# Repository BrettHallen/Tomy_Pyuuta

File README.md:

# Tomy Pyūta<br>トミーぴゅう太
Information about the Tomy Pyūta (TP1000), Pyūta Mk II (TP1007) and Pyūta Jr. (TP2001).  This computer was also seen in the West as the Tomy Tutor, but I don't have one of those and I'm sure there's plenty of English-language information already easily found.

Sorry about the mixed use of:
- ぴゅう太 (pyuuta)
- Pyuuta
- Pyuta
- Pyūta (pyuuta)
- Puuta (on motherboard)
- Mk II
- Mk 2
- mkII
- Mark 2
- Mark II
- etc.

### Pyūta TP1000

### Pyūta mkII TP1007
The motherboard names it as the TUTOR-MKII.

## YouTube Videos
### Pyūta (TP1000)
- [Part 1: Power On](https://youtu.be/n1GbW3sMFAQ)
- [Part 2: New Power Supply & Game Adaptor](https://youtu.be/_u84HEhmOtU)

### Pyūta mkII (TP1007)
- [Part 1: First Look](https://youtu.be/pd9VcPLzIxA)

## [Japanese G-BASIC Statements](/Japanese_G-BASIC)
My attempt at making sense of the unique Japanese version of BASIC (日本語G-BASIC) on the original ぴゅう太.

## [Universal Power Supply](/Tomy_Pyuuta_Power_Supply)
The Japanese ぴゅう太 is designed for a 100VAC input.<br>

The power supply outputs regulated +12VDC (via an LM7812), regulated -5VDC (via a TA78L005AP) and unregulated +5VDC (about +7.8V unloaded, 5.3V under load).  Yes, that is not a mistake ... the regulated -5V rail uses a 7805.<br>

The power LED is also connected to the -5V rail.<br>

I have designed a simple replacement as we use 240VAC here in Australia.<br>

It takes a regulated 12VDC input (3-4A) and generates the required ±5VDC via switching regulators, and passes the +12VDC straight through.<br>

## Pyūta mkII Video Mod
It seems that Tomy removed the baseband A/V output that was in the original TP1000 from the mkII, leaving it with just the RF modulated output.  I created a [quick schematic of the video output](/Schematics/Tomy_Pyuuta_mkII_AV) in the mkII to use as a basis, and found an [RC2014 expansion board that adds a TMS9918 video output](https://github.com/jblang/TMS9918A) which I could use as a reference.<br>

It seems to work okay!  I am planning to replace the TMS9918 with a [Pico9918](https://github.com/visrealm/pico9918) anyway.<br>

| Component | Original value | Modified value | Notes                                               |
|-----------|----------------|----------------|-----------------------------------------------------|
| R2        | 33Ω            | 75Ω            | Impedance matching                                  |
| R3        | 33Ω            | 0Ω link        |                                                     |
| R4        | 560Ω           | 470Ω           | Values are close, don't bother?                     |
| R5        | 8.2Ω           | Ferrite bead   |                                                     |
| C4        | 330pF          | 100nF to GND   | Connect from Q1 collector to GND                    |
| C49       | 47nF           | Remove         | 12V decoupling, not needed if RF modulator removed? |

## [Game Adaptor](/Pyuuta_Game_Adaptor)
My attempt at a homebrew version of the Pyūta Game Adaptor seeing as most of the information seems to have been lost.<br>

The Game Adaptor allows the original Pyūta (TP1000) to run 32KB cartridges designed for the Mk II (TP1007) and Jr. (TP2001).<br>

## Sources
- [yanataka60](https://github.com/yanataka60)

## Useful links
- [Floodgap Systems](https://www.floodgap.com/retrobits/tomy/)
- [Cartridge archive](https://www.classicplastic.net/helpline/)
- [Leaded Solder's Blog](https://www.leadedsolder.com/2023/03/14/tomy-pyuuta-pickup-keyboard-power-switch-repair.html)
- [Classic Plastic (software)](https://www.classicplastic.net/helpline/)

## [Recovered Info](/Recovered_Info)
Useful information I've found from either Japanese-language websites (so not easy for the non-Japanese to find) or from vanished websites that have been lost.  I absolutely do not claim any credit for the useful info contained.<br>

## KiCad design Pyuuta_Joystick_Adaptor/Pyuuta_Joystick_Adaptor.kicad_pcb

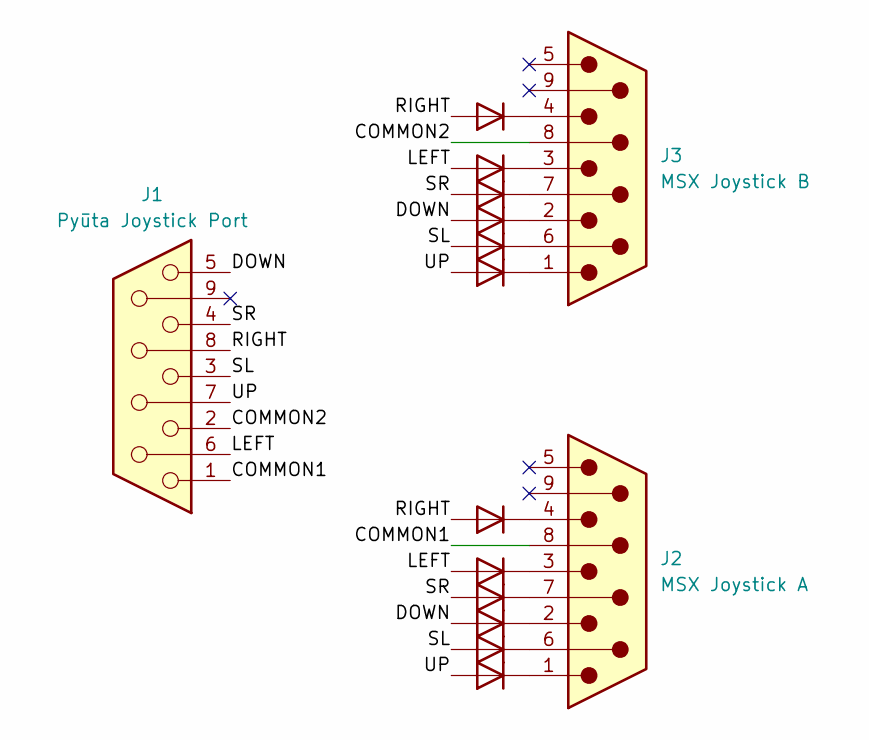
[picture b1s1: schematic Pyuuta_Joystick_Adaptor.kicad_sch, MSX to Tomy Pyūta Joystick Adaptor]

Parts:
D1, D2, D3, D4, D5, D6, D7, D8, D9, D10, D11, D12: 1N4148; D_SOD-323
J1: Pyūta Joystick Port; DSUB-9_Socket_Vertical_P2.77x2.84mm
J2: MSX Joystick A; DSUB-9_Pins_Vertical_P2.77x2.84mm
J3: MSX Joystick B; DSUB-9_Pins_Vertical_P2.77x2.84mm

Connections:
/COMMON1: J1.1, J2.8
/COMMON2: J1.2, J3.8
/DOWN: D3.2 (A), D10.2 (A), J1.5
/LEFT: D5.2 (A), D8.2 (A), J1.6
/RIGHT: D6.2 (A), D7.2 (A), J1.8
/SL: D2.2 (A), D11.2 (A), J1.3
/SR: D4.2 (A), D9.2 (A), J1.4
/UP: D1.2 (A), D12.2 (A), J1.7
unnamed: D1.1 (K), J2.1
unnamed: D2.1 (K), J2.6
unnamed: D3.1 (K), J2.2
unnamed: D4.1 (K), J2.7
unnamed: D5.1 (K), J2.3
unnamed: D6.1 (K), J2.4
unnamed: D7.1 (K), J3.4
unnamed: D8.1 (K), J3.3
unnamed: D9.1 (K), J3.7
unnamed: D10.1 (K), J3.2
unnamed: D11.1 (K), J3.6
unnamed: D12.1 (K), J3.1

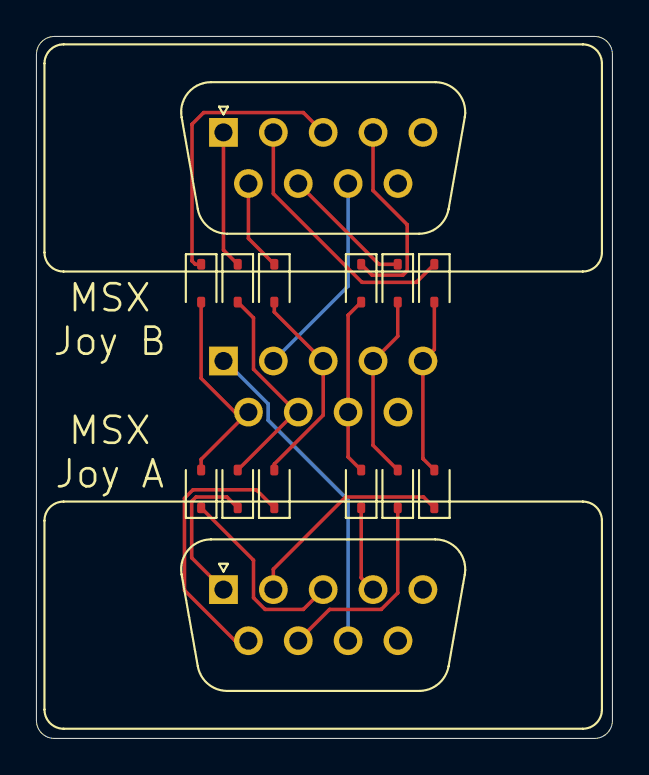
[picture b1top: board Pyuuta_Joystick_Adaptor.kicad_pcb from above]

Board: 2 copper layers, 32.0 x 39.0 mm, 15 parts (1 on the bottom side), 20 nets.

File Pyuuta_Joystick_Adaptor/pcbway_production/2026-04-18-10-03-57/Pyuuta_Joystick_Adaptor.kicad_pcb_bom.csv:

Designator,Quantity,Value,Footprint,Package,MPN,DNP,Mount_Type,Description,Sim.Device,Sim.Pins
"D1, D10, D11, D12, D2, D3, D4, D5, D6, D7, D8, D9",12,1N4148,D_SOD-323,,,,smt,Diode,D,1=K 2=A
J1,1,Pyūta Joystick Port,DSUB-9_Socket_Vertical_P2.77x2.84mm,,,,tht,"9-pin D-SUB connector, socket (female)",,
J2,1,MSX Joystick A,DSUB-9_Pins_Vertical_P2.77x2.84mm,,,,tht,"9-pin D-SUB connector, pins (male)",,
J3,1,MSX Joystick B,DSUB-9_Pins_Vertical_P2.77x2.84mm,,,,tht,"9-pin D-SUB connector, pins (male)",,

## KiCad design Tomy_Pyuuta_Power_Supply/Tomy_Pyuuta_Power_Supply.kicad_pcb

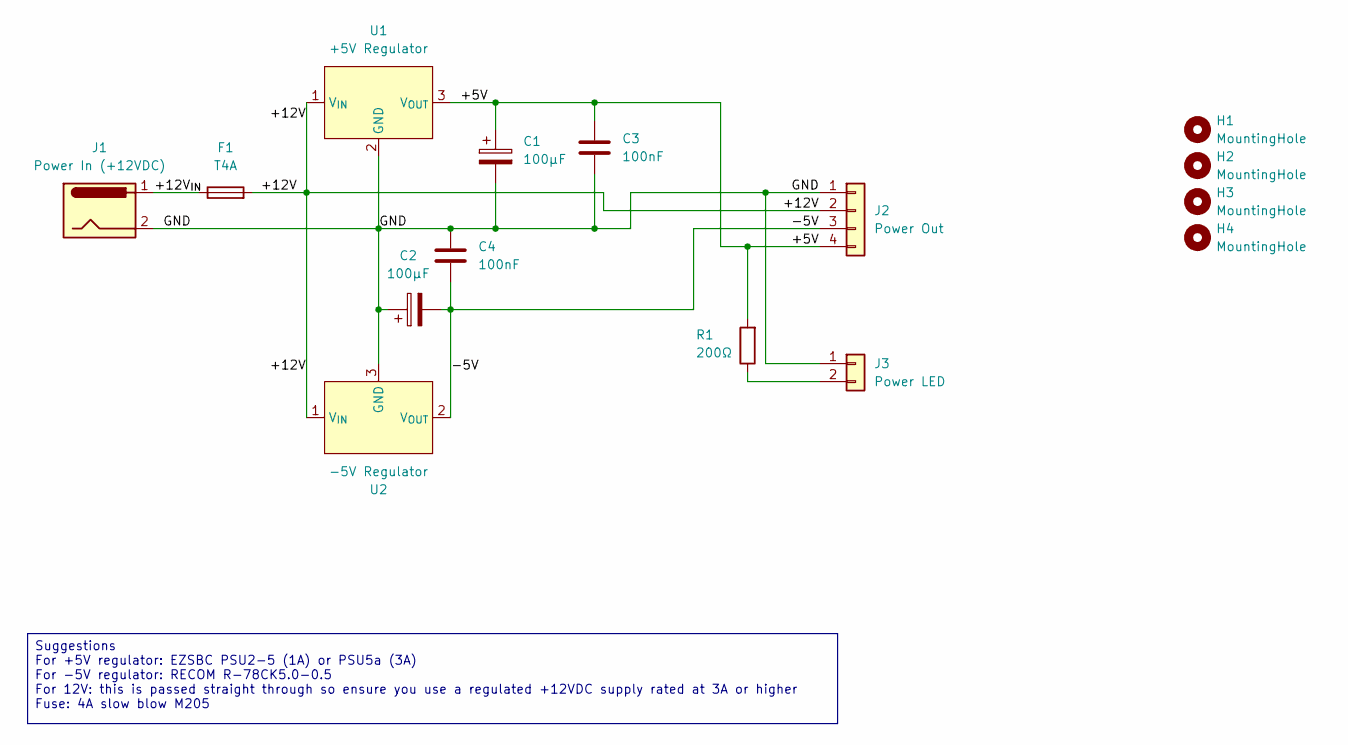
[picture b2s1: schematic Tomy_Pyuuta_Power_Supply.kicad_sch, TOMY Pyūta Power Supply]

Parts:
C1, C2: 100µF; CP_Radial_D6.3mm_P2.50mm
C3, C4: 100nF; C_Disc_D3.8mm_W2.6mm_P2.50mm
F1: T4A; Fuseholder_Clip-5x20mm_Littelfuse_111_Inline_P20.00x5.00mm_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
H1, H2, H3, H4: MountingHole; MountingHole_3.2mm_M3_DIN965
J1: Power In (+12VDC); JST_NV_B02P-NV_1x02_P5.00mm_Vertical
J2: Power Out; JST_NV_B04P-NV_1x04_P5.00mm_Vertical
J3: Power LED; PinHeader_1x02_P2.54mm_Vertical
R1: 200Ω; R_Axial_DIN0207_L6.3mm_D2.5mm_P10.16mm_Horizontal
U1: +5V Regulator; TO-220-3_Horizontal_TabDown
U2: -5V Regulator; R78CK5005; Manufacturer_Part_Number R-78CK5.0-0.5

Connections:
/+5V: C1.1, C3.1, J2.4, R1.2, U1.3 (V_{OUT})
/+12V: F1.2, J2.2, U1.1 (V_{IN}), U2.1 (V_{IN})
/+12V_{IN}: F1.1, J1.1
/-5V: C2.2, C4.1, J2.3, U2.2 (V_{OUT})
/GND: C1.2, C2.1, C3.2, C4.2, J1.2, J2.1, J3.1, U1.2 (GND), U2.3 (GND)
unnamed: J3.2, R1.1

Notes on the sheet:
Suggestions For +5V regulator: EZSBC PSU2-5 (1A) or PSU5a (3A) For -5V regulator: RECOM R-78CK5.0-0.5 For 12V: this is passed straight through so ensure you use a regulated +12VDC supply rated at 3A or higher Fuse: 4A slow blow M205

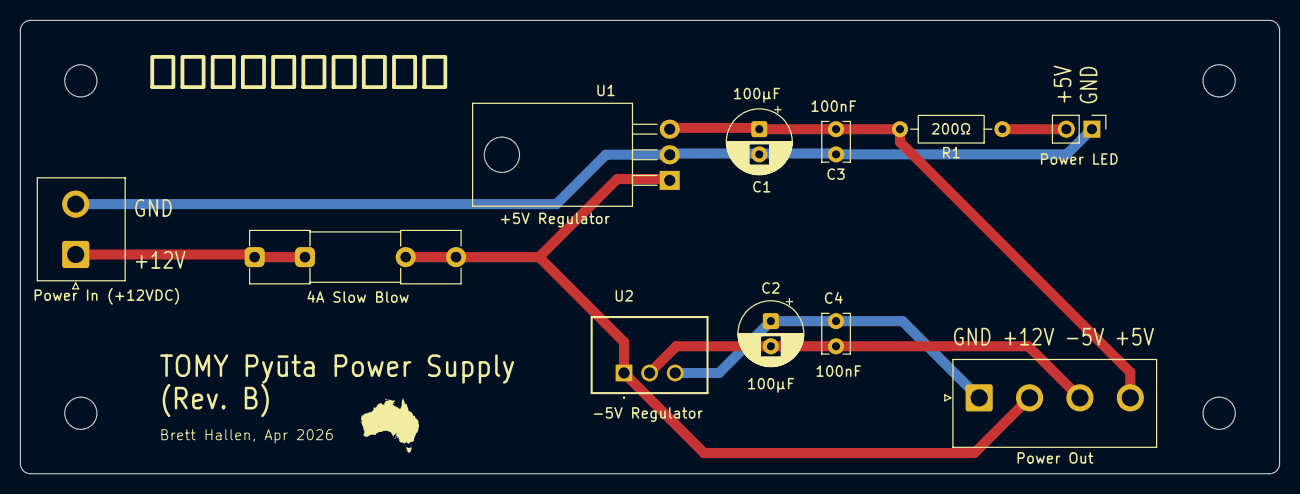
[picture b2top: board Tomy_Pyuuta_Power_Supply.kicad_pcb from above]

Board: 2 copper layers, 125.0 x 45.0 mm, 15 parts (0 on the bottom side), 6 nets.

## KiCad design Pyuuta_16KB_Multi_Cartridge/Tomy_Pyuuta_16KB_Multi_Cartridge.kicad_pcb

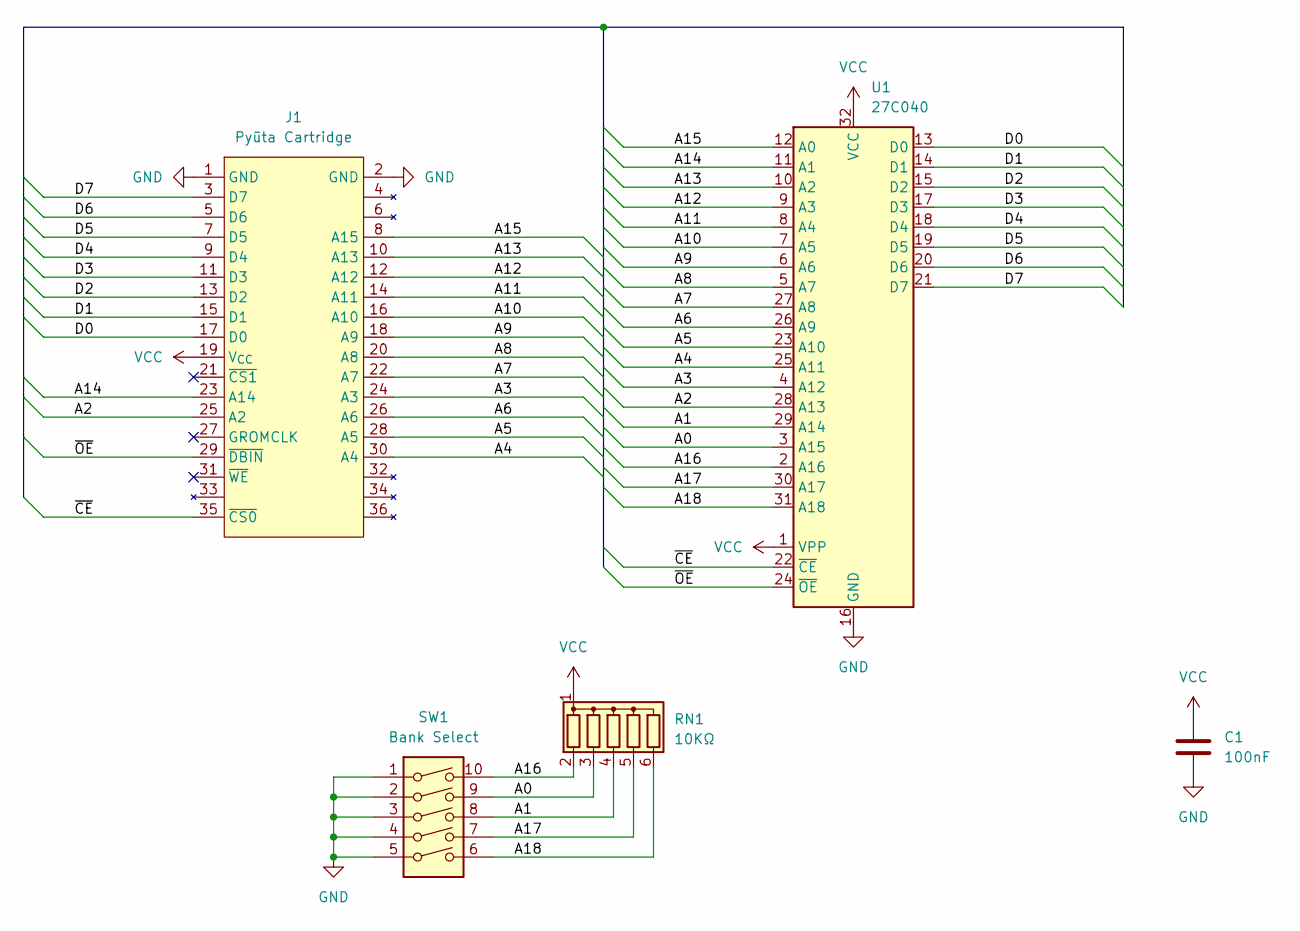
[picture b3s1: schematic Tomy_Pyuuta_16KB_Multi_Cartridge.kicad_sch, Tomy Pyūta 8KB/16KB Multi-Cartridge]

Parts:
C1: 100nF; C_Disc_D3.0mm_W1.6mm_P2.50mm
J1: Pyūta Cartridge; Tomy Pyūta Cartridge
RN1: 10KΩ; R_Array_SIP6
SW1: Bank Select; SW_DIP_SPSTx05_Slide_9.78x14.88mm_W7.62mm_P2.54mm
U1: 27C040; DIP-32_W15.24mm_LongPads

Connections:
/A0: RN1.3 (R2), SW1.9, U1.3 (A15)
/A1: RN1.4 (R3), SW1.8, U1.29 (A14)
/A2: J1.25 (A2), U1.28 (A13)
/A3: J1.24 (A3), U1.4 (A12)
/A4: J1.30 (A4), U1.25 (A11)
/A5: J1.28 (A5), U1.23 (A10)
/A6: J1.26 (A6), U1.26 (A9)
/A7: J1.22 (A7), U1.27 (A8)
/A8: J1.20 (A8), U1.5 (A7)
/A9: J1.18 (A9), U1.6 (A6)
/A10: J1.16 (A10), U1.7 (A5)
/A11: J1.14 (A11), U1.8 (A4)
/A12: J1.12 (A12), U1.9 (A3)
/A13: J1.10 (A13), U1.10 (A2)
/A14: J1.23 (A14), U1.11 (A1)
/A15: J1.8 (A15), U1.12 (A0)
/A16: RN1.2 (R1), SW1.10, U1.2 (A16)
/A17: RN1.5 (R4), SW1.7, U1.30 (A17)
/A18: RN1.6 (R5), SW1.6, U1.31 (A18)
/D0: J1.17 (D0), U1.13 (D0)
/D1: J1.15 (D1), U1.14 (D1)
/D2: J1.13 (D2), U1.15 (D2)
/D3: J1.11 (D3), U1.17 (D3)
/D4: J1.9 (D4), U1.18 (D4)
/D5: J1.7 (D5), U1.19 (D5)
/D6: J1.5 (D6), U1.20 (D6)
/D7: J1.3 (D7), U1.21 (D7)
/~CE: J1.35 (~CS0), U1.22 (~CE)
/~OE: J1.29 (~DBIN), U1.24 (~OE)
GND: C1.2, J1.1 (GND), J1.2 (GND), SW1.1, SW1.2, SW1.3, SW1.4, SW1.5, U1.16 (GND)
VCC: C1.1, J1.19 (V_{CC}), RN1.1 (common), U1.1 (VPP), U1.32 (VCC)

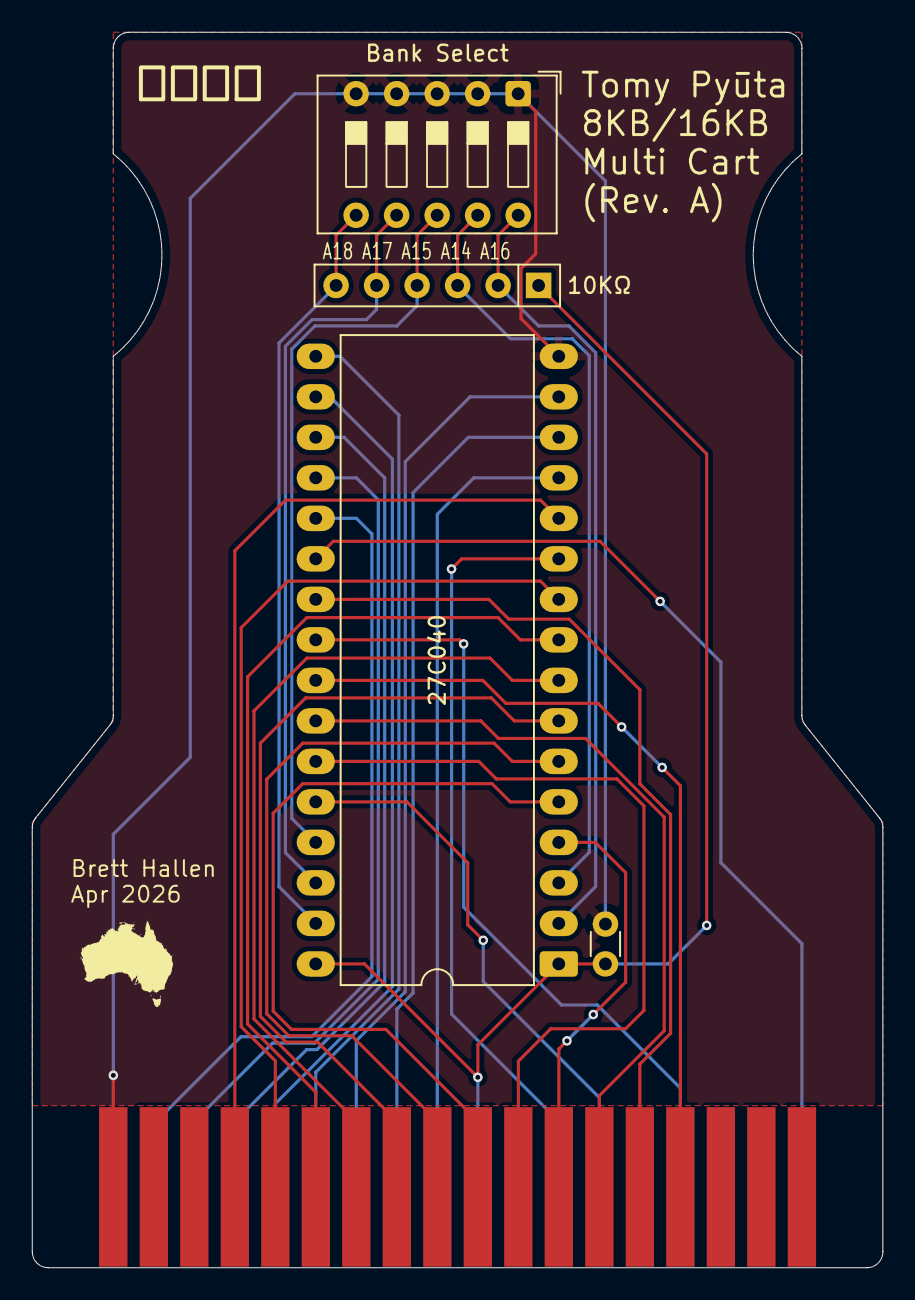
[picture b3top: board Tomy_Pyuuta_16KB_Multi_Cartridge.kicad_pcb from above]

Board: 2 copper layers, 53.3 x 77.5 mm, 5 parts (0 on the bottom side), 31 nets.

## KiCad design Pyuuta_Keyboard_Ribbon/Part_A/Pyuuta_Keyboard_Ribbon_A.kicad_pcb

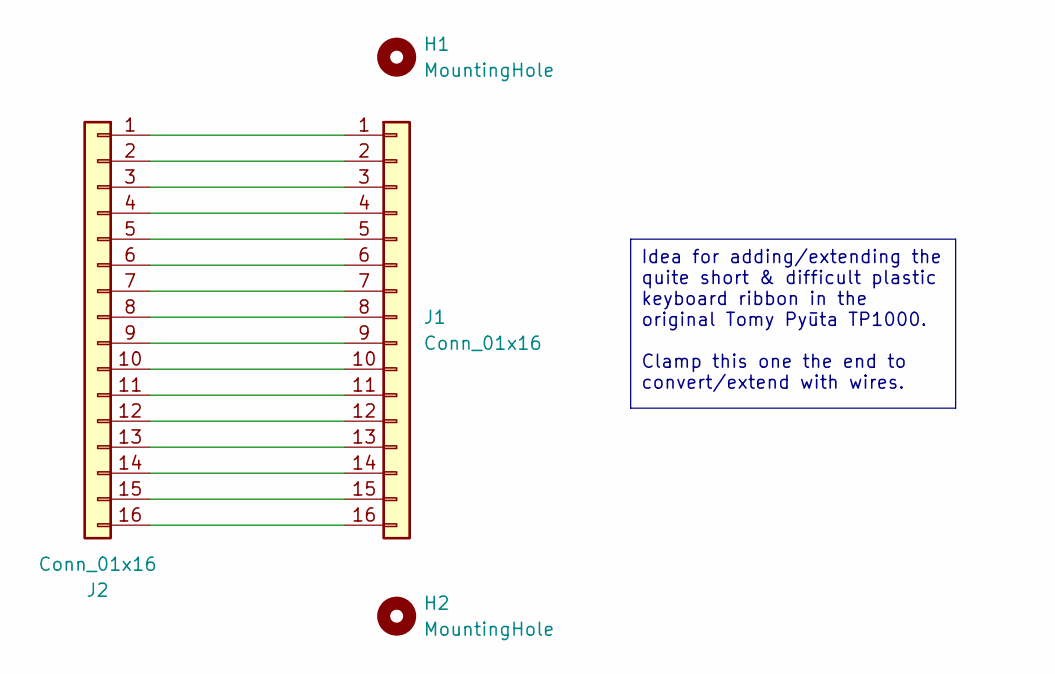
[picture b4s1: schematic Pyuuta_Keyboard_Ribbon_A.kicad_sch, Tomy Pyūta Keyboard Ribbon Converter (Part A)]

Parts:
H1, H2: MountingHole; MountingHole_3.2mm_M3
J1: Conn_01x16; PinHeader_1x16_P2.54mm_Vertical
J2: Conn_01x16; Tomy Pyuuta Keyboard

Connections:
unnamed: J1.1, J2.1
unnamed: J1.2, J2.2
unnamed: J1.3, J2.3
unnamed: J1.4, J2.4
unnamed: J1.5, J2.5
unnamed: J1.6, J2.6
unnamed: J1.7, J2.7
unnamed: J1.8, J2.8
unnamed: J1.9, J2.9
unnamed: J1.10, J2.10
unnamed: J1.11, J2.11
unnamed: J1.12, J2.12
unnamed: J1.13, J2.13
unnamed: J1.14, J2.14
unnamed: J1.15, J2.15
unnamed: J1.16, J2.16

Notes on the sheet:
Idea for adding/extending the quite short & difficult plastic keyboard ribbon in the original Tomy Pyūta TP1000. Clamp this one the end to convert/extend with wires.

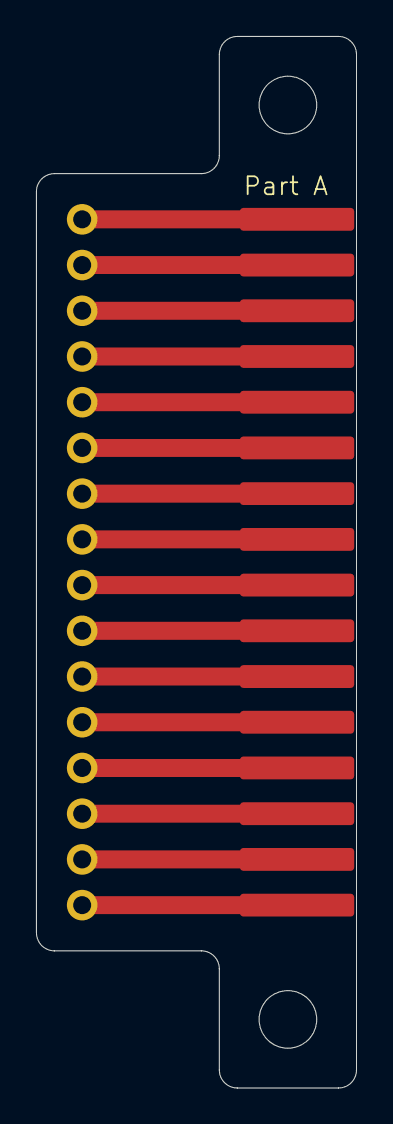
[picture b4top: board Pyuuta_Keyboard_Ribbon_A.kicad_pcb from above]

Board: 2 copper layers, 17.8 x 58.4 mm, 4 parts (0 on the bottom side), 16 nets.

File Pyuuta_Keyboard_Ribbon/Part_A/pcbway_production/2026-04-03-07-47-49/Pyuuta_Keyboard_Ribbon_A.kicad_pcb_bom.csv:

Designator,Quantity,Value,Footprint,Package,MPN,DNP,Mount_Type,Description
J1,1,Conn_01x16,PinHeader_1x16_P2.54mm_Vertical,,,,tht,"Generic connector, single row, 01x16, script generated (kicad-library-utils/schlib/autogen/connector/)"
J2,1,Conn_01x16,Tomy Pyuuta Keyboard,,,,tht,"Generic connector, single row, 01x16, script generated (kicad-library-utils/schlib/autogen/connector/)"

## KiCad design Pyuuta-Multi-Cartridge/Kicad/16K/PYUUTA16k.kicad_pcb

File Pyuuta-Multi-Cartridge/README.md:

# TOMY Pyūta Multi Cartridge
Original repository (Japanese):<br>
https://github.com/yanataka60/PYUTA-GBASIC-Multi-Cartridge

Inufutoさん has generously published many self-made programs for retro PCs, and for the ぴゅう太 (Pyūta) they are released as ROM images.

So [I (yanataka60)](https://github.com/yanataka60) created a cartridge that allows you to easily switch between those ROM images using DIP switches and enjoy them on real hardware.

The published ROM images come in two types: (>8000～) and (>4000～).  
Use the **16KB (8KB) ROM Multi Cartridge** for (>8000～) images and the **32KB ROM Multi Cartridge** for (>4000～) images.

**Note:** To use the 32KB ROM Multi Cartridge on the original (first-generation) ぴゅう太, a game adapter equivalent is required.  
Inserting the 32KB ROM Multi Cartridge directly into the original ぴゅう太 cartridge slot will **not** work.

The 16KB (8KB) ROM Multi Cartridge has been tested working on ぴゅう太 and ぴゅう太 mk2.  
The 32KB ROM Multi Cartridge has been tested working on ぴゅう太 + game adapter equivalent, and ぴゅう太 mk2.  
Both types are expected to work on the ぴゅう太 Jr. as well.

Of course, you will need a separate ROM programmer/writer device to burn the images into the EPROMs.

## 16KB (8KB) ROM Multi Cartridge

### Schematic
Please refer to `PYUTA16k.pdf` in the KiCad folder.

[ schematic ](https://github.com/yanataka60/PYUTA-Multi-Cartridge/blob/main/Kicad/16K/PYUTA16k.pdf)

### Parts List

| Ref  | Part name                        | Qty | Notes                              |
|------|----------------------------------|-----|------------------------------------|
| U1–U4| ROM 27512                        | 1–4 | Up to 4 pieces                     |
| U5   | 74LS138                          | 1   |                                    |
| U6   | 74LS32                           | 1   |                                    |
| SW1  | DIP switch 4-position            | 1   | e.g. Akizuki EDS104SZ etc.         |
| R1–R4| Carbon resistor 10KΩ             | 4   |                                    |
| C1–C4, C6, C7 | Multilayer ceramic capacitor 100nF | 6 | |
| C5   | Electrolytic capacitor 16V 100µF | 1 | |
|      | 28-pin IC socket                 | 4   |                                    |
|      | 16-pin IC socket                 | 1   | Optional                           |
|      | 14-pin IC socket                 | 1   | Optional                           |

### Writing to ROM
Write the ROM images to each 27512 starting at the following addresses:
- 0000h
- 4000h
- 8000h
- C000h

### ROM Image Selection
- DIP switch positions 1 and 2 select the bank: 0000h / 4000h / 8000h / C000h  
- DIP switch positions 3 and 4 select which ROM chip (U1–U4) is active.

Up to **16 different ROM images** can be selected.

## 32KB ROM Multi Cartridge

### Schematic
Please refer to `PYUTA32k.pdf` in the KiCad folder.

[ schematic ](https://github.com/yanataka60/PYUTA-Multi-Cartridge/blob/main/Kicad/32K/PYUTA32k.pdf)

### Parts List

| Ref  | Part name                        | Qty | Notes                              |
|------|----------------------------------|-----|------------------------------------|
| U1–U4| ROM 27512                        | 1–4 | Up to 4 pieces                     |
| U5   | 74LS138                          | 1   |                                    |
| U6   | 74LS32                           | 1   |                                    |
| U7   | 74LS04                           | 1   |                                    |
| U8   | 74LS08                           | 1   |                                    |
| SW1  | DIP switch 4-position            | 1   | Akizuki EDS104SZ etc. (only 3 bits used, 3-position switch is also OK) |
| R2–R4| Carbon resistor 10KΩ            | 3   |                                    |
| C1–C4, C6–C9 | Multilayer ceramic capacitor 100nF | 8 | |
| C5   | Electrolytic capacitor 16V 100µF | 1 | |
|      | 28-pin IC socket                 | 4   |                                    |
|      | 16-pin IC socket                 | 1   | Optional                           |
|      | 14-pin IC socket                 | 3   | Optional                           |

### Writing to ROM
Write the ROM images to each 27512 starting at the following addresses:
- 0000h
- 8000h

### ROM Image Selection
- DIP switch position 1 selects the bank: 0000h / 8000h  
- DIP switch positions 2 and 3 select which ROM chip (U1–U4) is active.

Up to **eight different ROM images** can be selected.

## Acknowledgements
Thank you very much to Inufutoさま for releasing so many wonderful games.<br>
Thank you to Enriさま for publishing detailed technical information about the ぴゅう太.<br>
And thanks to yanataka60 for kindly making his design available.

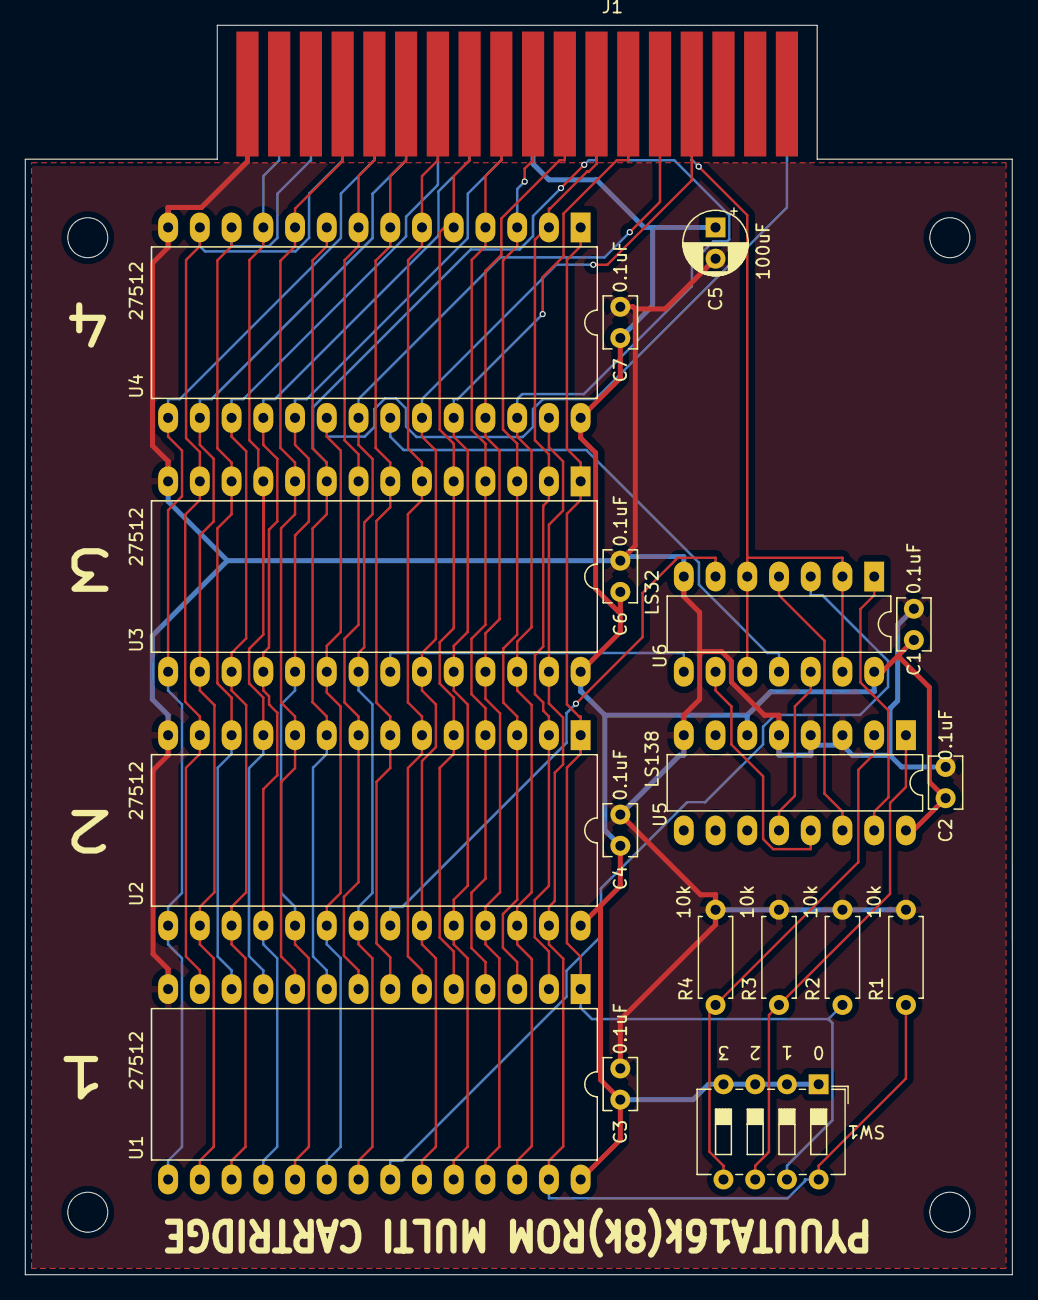
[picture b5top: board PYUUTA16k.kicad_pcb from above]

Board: 2 copper layers, 79.0 x 100.0 mm, 23 parts (0 on the bottom side), 38 nets.

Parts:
C1, C2, C3, C4, C6, C7: 0.1uF; C_Rect_L4.0mm_W2.5mm_P2.50mm
C5: 100uF; CP_Radial_D5.0mm_P2.50mm
J1: PYUUTA CART; BUS_36Pin
MH1, MH2, MH3, MH4: MountingHole_3.2mm_M3
R1, R2, R3, R4: 10k; R_Axial_DIN0207_L6.3mm_D2.5mm_P7.62mm_Horizontal
SW1: SW_DIP_x04; SW_DIP_SPSTx04_Slide_6.7x11.72mm_W7.62mm_P2.54mm_LowProfile
U1, U2, U3, U4: 27C512; DIP-28_W15.24mm_LongPads
U5: 74LS138; DIP-16_W7.62mm_LongPads
U6: 74LS32; DIP-14_W7.62mm_LongPads

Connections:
+5V: C1.1, C2.2, C3.2, C4.2, C5.1, C6.2, C7.2, J1.19, SW1.1, SW1.2, SW1.3, SW1.4, U1.28, U2.28, U3.28, U4.28, U5.6, U5.16, U6.14
/A2: J1.25, U1.26, U2.26, U3.26, U4.26
/A3: J1.24, U1.2, U2.2, U3.2, U4.2
/A4: J1.30, U1.23, U2.23, U3.23, U4.23
/A5: J1.28, U1.21, U2.21, U3.21, U4.21
/A6: J1.26, U1.24, U2.24, U3.24, U4.24
/A7: J1.22, U1.25, U2.25, U3.25, U4.25
/A8: J1.20, U1.3, U2.3, U3.3, U4.3
/A9: J1.18, U1.4, U2.4, U3.4, U4.4
/A10: J1.16, U1.5, U2.5, U3.5, U4.5
/A11: J1.14, U1.6, U2.6, U3.6, U4.6
/A12: J1.12, U1.7, U2.7, U3.7, U4.7
/A13: J1.10, U1.8, U2.8, U3.8, U4.8
/A14: J1.23, U1.9, U2.9, U3.9, U4.9
/A15: J1.8, U1.10, U2.10, U3.10, U4.10
/D0: J1.17, U1.19, U2.19, U3.19, U4.19
/D1: J1.15, U1.18, U2.18, U3.18, U4.18
/D2: J1.13, U1.17, U2.17, U3.17, U4.17
/D3: J1.11, U1.16, U2.16, U3.16, U4.16
/D4: J1.9, U1.15, U2.15, U3.15, U4.15
/D5: J1.7, U1.13, U2.13, U3.13, U4.13
/D6: J1.5, U1.12, U2.12, U3.12, U4.12
/D7: J1.3, U1.11, U2.11, U3.11, U4.11
/~CS0: J1.35, U1.20, U2.20, U3.20, U4.20
/~DBIN: J1.29, U6.2, U6.5, U6.10, U6.13
GND: C1.2, C2.1, C3.1, C4.1, C5.2, C6.1, C7.1, J1.1, J1.2, R1.2, R2.2, R3.2, R4.2, U1.14, U2.14, U3.14, U4.14, U5.3, U5.4, U5.5, U5.8, U6.7
unnamed: R1.1, SW1.8, U1.27, U2.27, U3.27, U4.27
unnamed: R2.1, SW1.7, U1.1, U2.1, U3.1, U4.1
unnamed: R3.1, SW1.6, U5.1
unnamed: R4.1, SW1.5, U5.2
unnamed: U1.22, U6.3
unnamed: U2.22, U6.6
unnamed: U3.22, U6.8
unnamed: U4.22, U6.11
unnamed: U5.12, U6.12
unnamed: U5.13, U6.9
unnamed: U5.14, U6.4
unnamed: U5.15, U6.1

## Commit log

2026-03-11 Added fuse holder 3D
2026-03-12 Initial commit of images
2026-03-13 Updated from actual Game Adaptor
2026-03-13 Game Adaptor photos
2026-03-14 Initial design completed
2026-03-14 Added part IDs
2026-03-15 Added info about unused parts to schematic
2026-03-30 Renamed PYUTA to PYUUTA
2026-03-30 Fixed 5V regulator pinout
2026-04-03 Initial commit - work in progress
2026-04-03 Idea for keyboard ribbon cable repair
2026-04-03 Updated power connecters to JST
2026-04-03 Routing changes
2026-04-06 Added video mod details
2026-04-12 Artwork update
2026-04-12 PCB artwork update
